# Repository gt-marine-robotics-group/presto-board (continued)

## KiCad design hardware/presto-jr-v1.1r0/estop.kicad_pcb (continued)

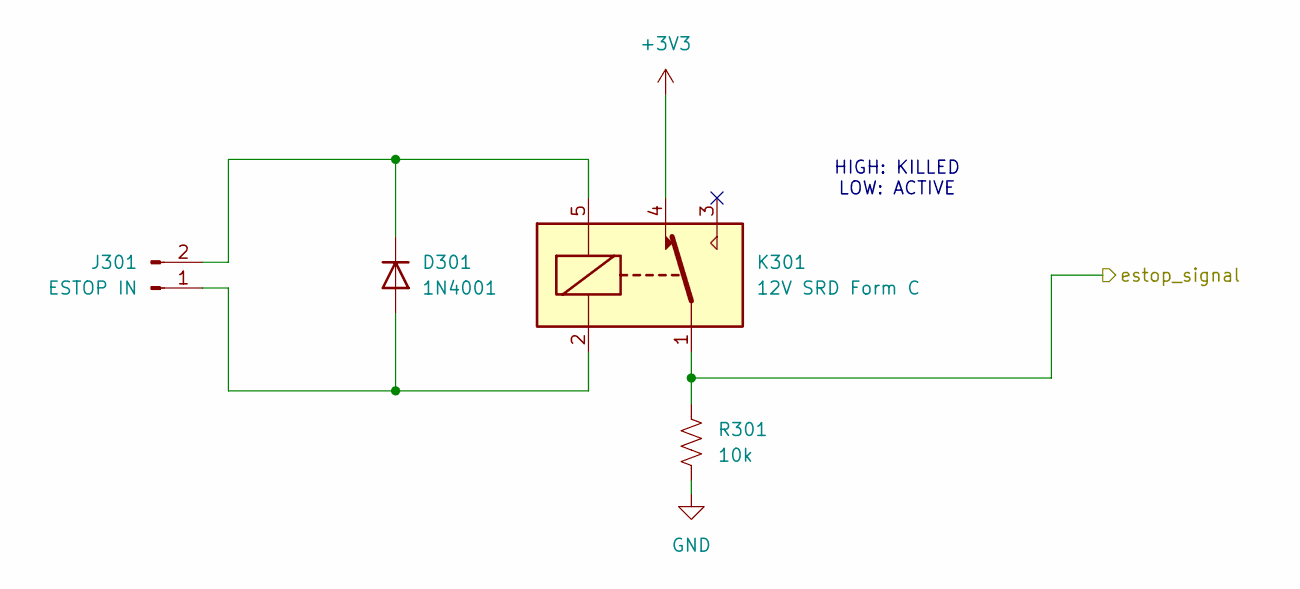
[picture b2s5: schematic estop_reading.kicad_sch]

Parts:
D301: 1N4001; D_DO-41_SOD81_P10.16mm_Horizontal
J301: ESTOP IN; AMASS_XT30PW-M_1x02_P2.50mm_Horizontal
K301: 12V SRD Form C; Relay_SPDT_SANYOU_SRD_Series_Form_C
R301: 10k; R_Axial_DIN0207_L6.3mm_D2.5mm_P10.16mm_Horizontal

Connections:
+3V3: K301.4; also elsewhere on the board
/EStop Reading/estop_signal: K301.1, R301.1; also elsewhere on the board
GND: R301.2; also elsewhere on the board
unnamed: D301.2 (A), J301.1, K301.2
unnamed: D301.1 (K), J301.2, K301.5

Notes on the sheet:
HIGH: KILLED LOW: ACTIVE

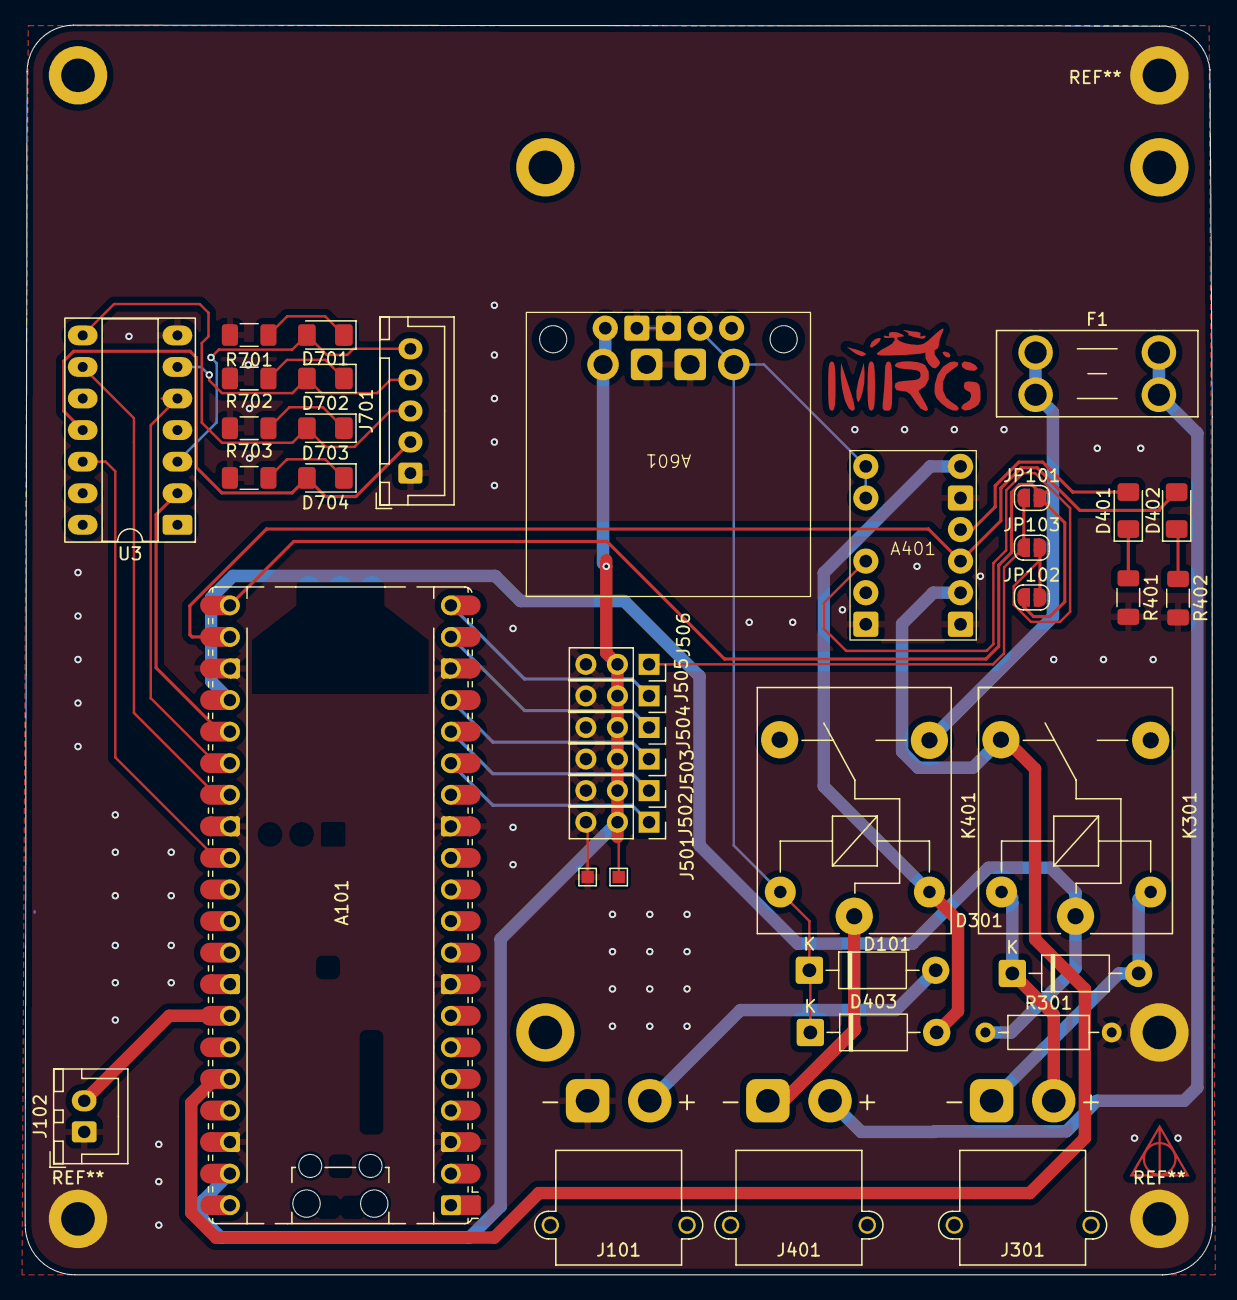
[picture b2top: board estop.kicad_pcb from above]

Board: 2 copper layers, 95.5 x 100.5 mm, 37 parts (0 on the bottom side), 37 nets.

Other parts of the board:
A601: Pololu 5V 3A Regulator S13V30F5; Pololu_S13V30F5

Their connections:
+5V: A601.5 (VOUT); also elsewhere on the board
+12V: A601.2 (VIN); also elsewhere on the board
GND: A601.3 (GND), A601.4 (GND); also elsewhere on the board

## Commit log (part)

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2025-09-25 Added kicad project
2025-09-25 Minor document changes
2025-10-01 RC and Servo interface schematic done
2025-10-08 Added estop, power, led schematics
2025-10-08 Presto PCB edited with schematic, components placed, wiring in progress
2025-10-19 Presto PCB all wired up, please let me know if any changes are necessary
2025-10-22 Presto PCB wired up with most changes implemented + filled zone
2025-10-22 LED diode traces not connected properly, deleted, needs to be fixed
2025-10-23 Rearranged to accomodate JST
2025-10-27 Fixed double hole
2025-11-07 2-pin JST added for autonomous, 6 routes not connected for some reason though
2026-03-06 added connector for neopixel and fixed autonomy switch layout
2026-03-11 added fuse and changed revision number
2026-05-04 added autonomy switch to presto for robosub
2026-05-04 reorganized and brought in presto jr
2026-05-04 Enhance README with variant descriptions and firmware link
    Added descriptions for Presto and Presto Jr. variants, and included a link to the firmware.
2026-05-06 reshaped and added v2
2026-05-07 updated v2
2026-06-23 added presto jr
2026-06-23 update libraries to kicad10
